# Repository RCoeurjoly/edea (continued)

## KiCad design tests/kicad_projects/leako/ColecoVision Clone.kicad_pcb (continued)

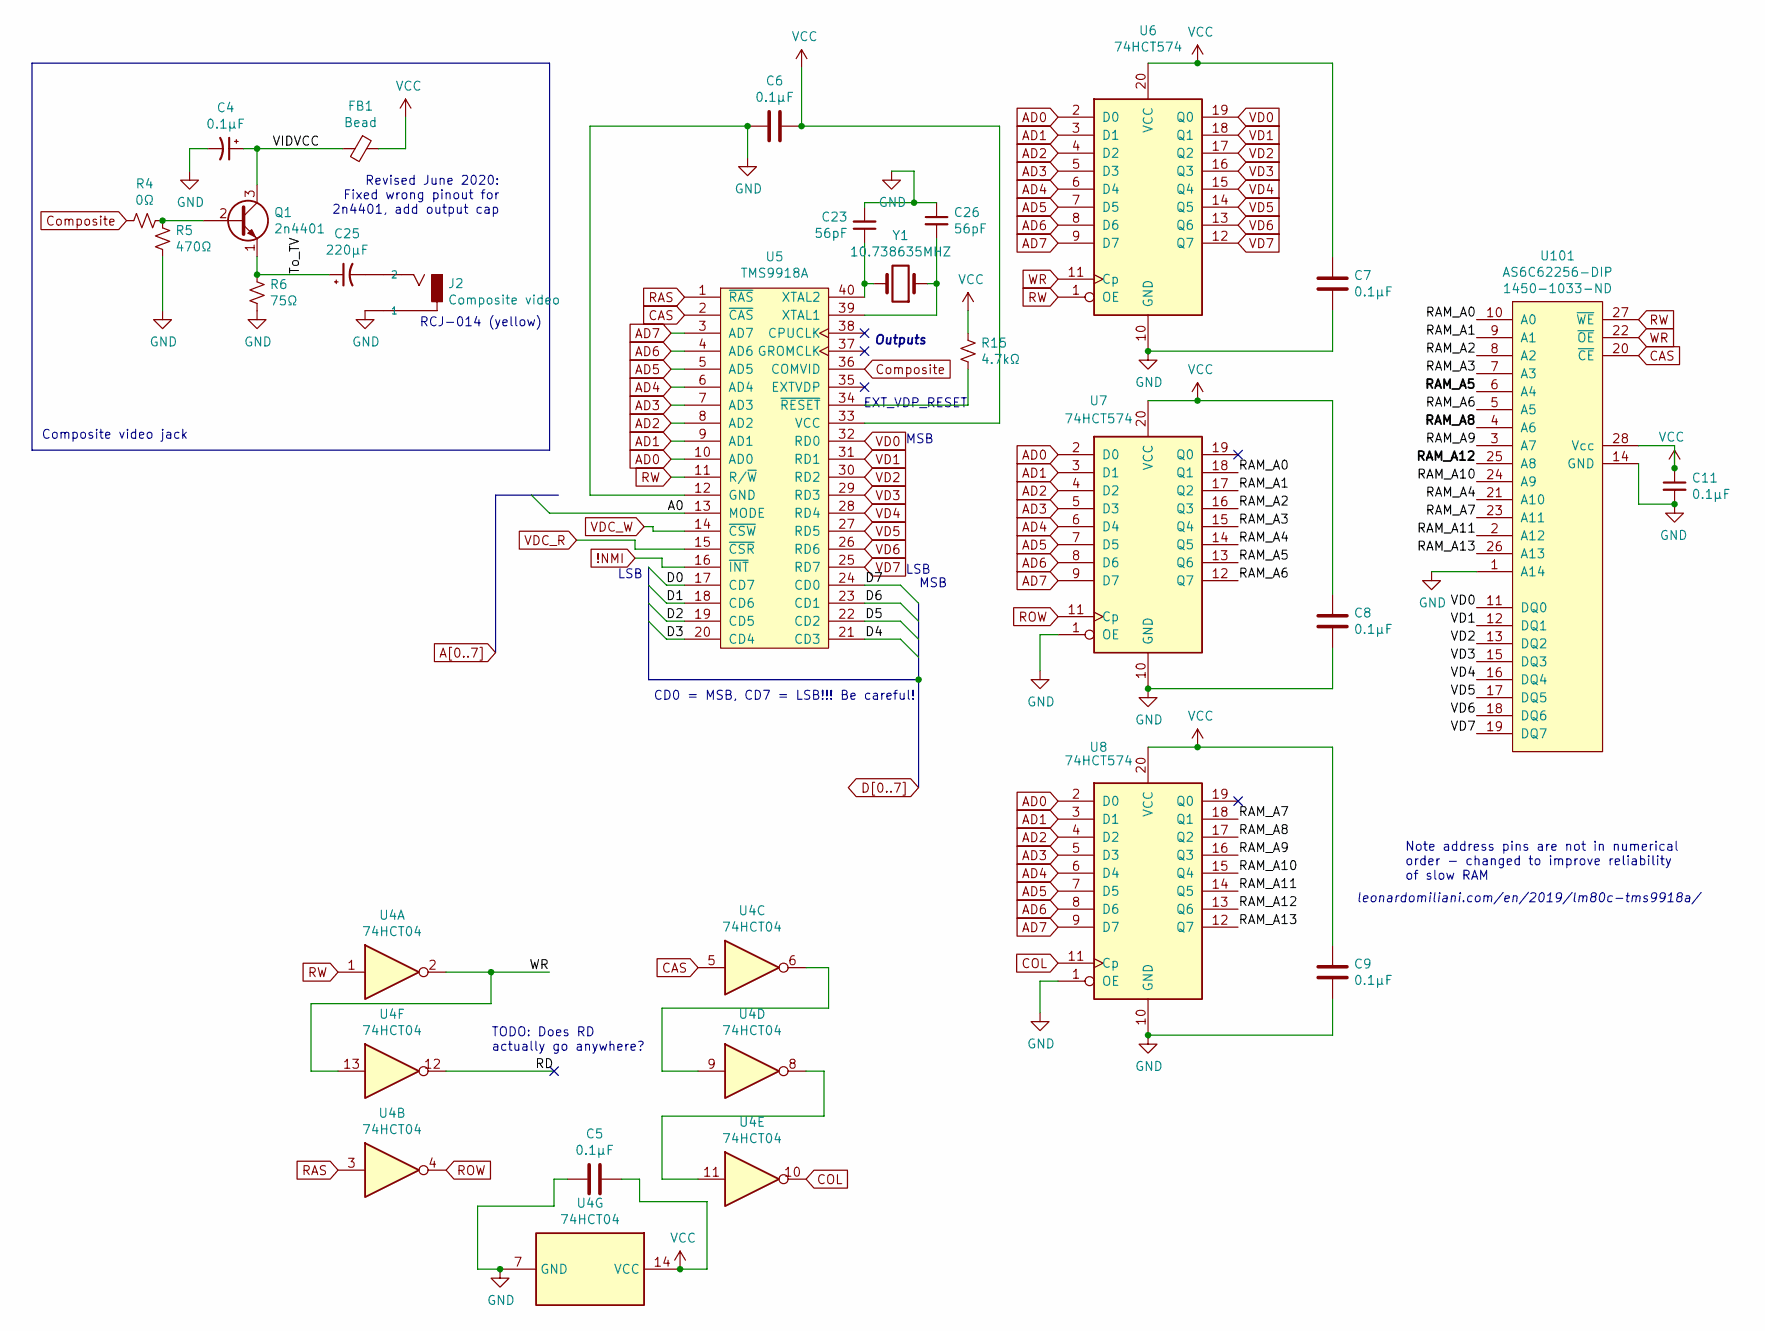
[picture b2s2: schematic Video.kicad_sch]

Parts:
C4, C5, C6, C7, C8, C9, C11: 0.1µF; C_0805_HandSoldering; DigiKey 1276-1099-1-ND
C23, C26: 56pF; C_0805_HandSoldering; DigiKey 732-7817-1-ND
C25: 220µF; CP_Radial_D6.3mm_P2.50mm; DigiKey 493-15121-ND
FB1: Bead; Choke_SMD_1206_Handsoldering; DigiKey 283-MFBW1V3216-310-RCT-ND
J2: Composite video; CUI_RCJ-017; DigiKey CP-1403-ND‎
Q1: 2n4401; TO-92_Inline_Wide; DigiKey 2N4401TFCT-ND
R4: 0Ω; R_0805_HandSoldering; DigiKey RMCF0805ZT0R00CT-ND
R5: 470Ω; R_0805_HandSoldering; DigiKey RMCF0805JT470RCT-ND
R6: 75Ω; R_0805_HandSoldering; DigiKey RMCF0805JT75R0CT-ND
R15: 4.7kΩ; R_0805_HandSoldering; DigiKey RMCF0805JT4K70CT-ND
U4: 74HCT04; SOIC-14_3.9x8.7mm_Pitch1.27mm; DigiKey 296-31832-1-ND
U5: TMS9918A; DIP-40_W15.24mm_Socket_LongPads; DigiKey ED3048-5-ND
U6, U7, U8: 74HCT574; SOIC-20W_7.5x12.8mm_P1.27mm_LongLegs; DigiKey 1727-2856-1-ND
U101: AS6C62256-DIP; DIP-28_W15.24mm_Socket_LongPads; DigiKey 1450-1033-ND
Y1: 10.738635MHZ; Crystal_HC49-U_Vertical; DigiKey CTX1443-ND

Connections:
!NMI: U5.16 (~INT); also elsewhere on the board
/Video/RAM_A0: U7.18 (Q1), U101.10 (A0)
/Video/RAM_A1: U7.17 (Q2), U101.9 (A1)
/Video/RAM_A2: U7.16 (Q3), U101.8 (A2)
/Video/RAM_A3: U7.15 (Q4), U101.7 (A3)
/Video/RAM_A4: U7.14 (Q5), U101.21 (A10)
/Video/RAM_A5: U7.13 (Q6), U101.6 (A4)
/Video/RAM_A6: U7.12 (Q7), U101.5 (A5)
/Video/RAM_A7: U8.18 (Q1), U101.23 (A11)
/Video/RAM_A8: U8.17 (Q2), U101.4 (A6)
/Video/RAM_A9: U8.16 (Q3), U101.3 (A7)
/Video/RAM_A10: U8.15 (Q4), U101.24 (A9)
/Video/RAM_A11: U8.14 (Q5), U101.2 (A12)
/Video/RAM_A12: U8.13 (Q6), U101.25 (A8)
/Video/RAM_A13: U8.12 (Q7), U101.26 (A13)
/Video/RD: U4.12
/Video/To_TV: C25.1, Q1.1 (E), R6.1
/Video/VIDVCC: C4.1, FB1.2, Q1.3 (C)
A0: U5.13 (MODE); also elsewhere on the board
AD0: U5.10 (AD0), U6.2 (D0), U7.2 (D0), U8.2 (D0)
AD1: U5.9 (AD1), U6.3 (D1), U7.3 (D1), U8.3 (D1)
AD2: U5.8 (AD2), U6.4 (D2), U7.4 (D2), U8.4 (D2)
AD3: U5.7 (AD3), U6.5 (D3), U7.5 (D3), U8.5 (D3)
AD4: U5.6 (AD4), U6.6 (D4), U7.6 (D4), U8.6 (D4)
AD5: U5.5 (AD5), U6.7 (D5), U7.7 (D5), U8.7 (D5)
AD6: U5.4 (AD6), U6.8 (D6), U7.8 (D6), U8.8 (D6)
AD7: U5.3 (AD7), U6.9 (D7), U7.9 (D7), U8.9 (D7)
CAS: U4.5, U5.2 (~CAS), U101.20 (~CE)
COL: U4.10, U8.11 (Cp)
Composite: R4.2, U5.36 (COMVID)
D0: U5.17 (CD7); also elsewhere on the board
D1: U5.18 (CD6); also elsewhere on the board
D2: U5.19 (CD5); also elsewhere on the board
D3: U5.20 (CD4); also elsewhere on the board
D4: U5.21 (CD3); also elsewhere on the board
D5: U5.22 (CD2); also elsewhere on the board
D6: U5.23 (CD1); also elsewhere on the board
D7: U5.24 (CD0); also elsewhere on the board
GND: C4.2, C5.2, C6.2, C7.2, C8.2, C9.2, C11.2, C23.2, C26.1, J2.1A (1), J2.1B (1), J2.1C (1), R5.2, R6.2, U4.7 (GND), U5.12 (GND), U6.10 (GND), U7.1 (OE), U7.10 (GND), U8.1 (OE), U8.10 (GND), U101.1 (A14), U101.14 (GND); also elsewhere on the board
unnamed: C23.1, U5.40 (XTAL2), Y1.2
unnamed: C25.2, J2.2
unnamed: C26.2, U5.39 (XTAL1), Y1.1
unnamed: Q1.2 (B), R4.1, R5.1
unnamed: R15.2, U5.34 (~RESET)
unnamed: U4.6, U4.9
unnamed: U4.8, U4.11
RAS: U4.3, U5.1 (~RAS)
ROW: U4.4, U7.11 (Cp)
RW: U4.1, U5.11 (R/~W), U6.1 (OE), U101.27 (~WE)
VCC: C5.1, C6.1, C7.1, C8.1, C9.1, C11.1, FB1.1, R15.1, U4.14 (VCC), U5.33 (VCC), U6.20 (VCC), U7.20 (VCC), U8.20 (VCC), U101.28 (Vcc); also elsewhere on the board
VD0: U5.32 (RD0), U6.19 (Q0), U101.11 (DQ0)
VD1: U5.31 (RD1), U6.18 (Q1), U101.12 (DQ1)
VD2: U5.30 (RD2), U6.17 (Q2), U101.13 (DQ2)
VD3: U5.29 (RD3), U6.16 (Q3), U101.15 (DQ3)
VD4: U5.28 (RD4), U6.15 (Q4), U101.16 (DQ4)
VD5: U5.27 (RD5), U6.14 (Q5), U101.17 (DQ5)
VD6: U5.26 (RD6), U6.13 (Q6), U101.18 (DQ6)
VD7: U5.25 (RD7), U6.12 (Q7), U101.19 (DQ7)
VDC_R: U5.15 (~CSR); also elsewhere on the board
VDC_W: U5.14 (~CSW); also elsewhere on the board
WR: U4.2, U4.13, U6.11 (Cp), U101.22 (~OE)

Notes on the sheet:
leonardomiliani.com/en/2019/lm80c-tms9918a/
TODO: Does RD actually go anywhere?
EXT_VDP_RESET
LSB
CD0 = MSB, CD7 = LSB!!! Be careful!
Composite video jack
Note address pins are not in numerical order - changed to improve reliability of slow RAM
RCJ-014 (yellow)
Revised June 2020: Fixed wrong pinout for 2n4401, add output cap
MSB
Outputs

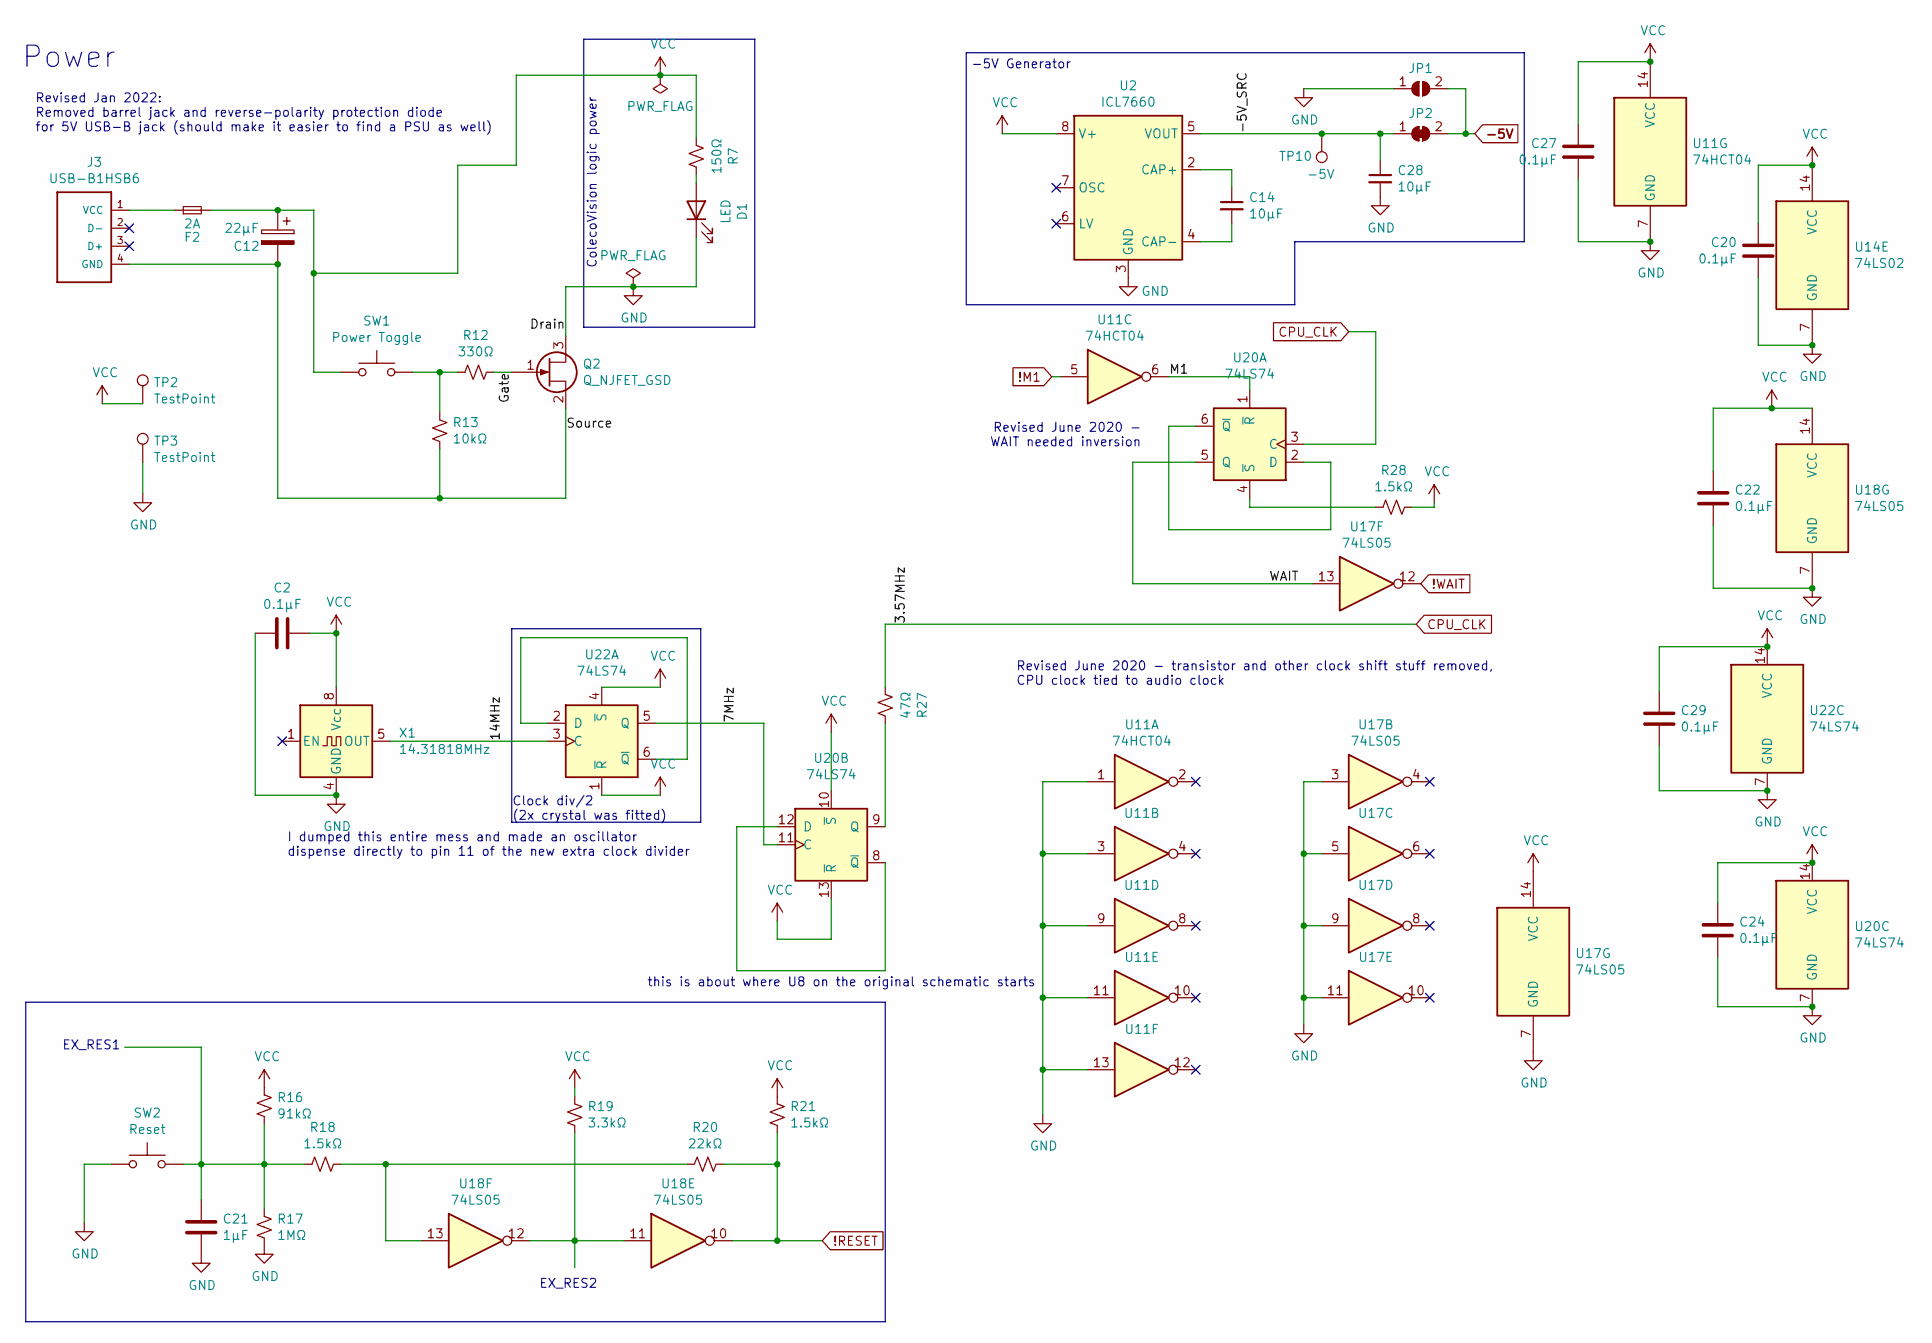
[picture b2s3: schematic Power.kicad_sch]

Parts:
C2, C20, C22, C24, C27, C29: 0.1µF; C_0805_HandSoldering; DigiKey 1276-1099-1-ND
C12: 22µF; CP_Radial_D5.0mm_P2.50mm; DigiKey 493-1037-ND
C14, C28: 10µF; C_0805_2012Metric_Pad1.15x1.40mm_HandSolder; DigiKey 1276-1298-1-ND
C21: 1µF; C_0805_HandSoldering; DigiKey 1276-2926-1-ND
D1: LED; LED_D3.0mm; DigiKey 1497-1022-ND
F2: 2A; 0251002.MRT1L; DigiKey F3171CT-ND
J3: USB-B1HSB6; OST_USB-B1HSB6; DigiKey ED2982-ND
JP1: SolderJumper_2_Open; SolderJumper-2_P1.3mm_Open_Pad1.0x1.5mm
JP2: SolderJumper_2_Bridged; SolderJumper-2_P1.3mm_Bridged_Pad1.0x1.5mm
Q2: Q_NJFET_GSD; SOT-23_Handsoldering; DigiKey DMN2046U-7DICT-ND
R7: 150Ω; R_0805_HandSoldering; DigiKey RMCF0805JT150RCT-ND
R12: 330Ω; R_0805_HandSoldering; DigiKey RMCF0805JT330RCT-ND
R13: 10kΩ; R_0805_HandSoldering; DigiKey RMCF0805JT10K0CT-ND
R16: 91kΩ; R_0805_HandSoldering; DigiKey RMCF0805JT91K0CT-ND
R17: 1MΩ; R_0805_HandSoldering; DigiKey RMCF0805JT1M00CT-ND
R18, R21, R28: 1.5kΩ; R_0805_HandSoldering; DigiKey RMCF0805FT1K00CT-ND
R19: 3.3kΩ; R_0805_HandSoldering; DigiKey RMCF0805JT3K30CT-ND
R20: 22kΩ; R_0805_HandSoldering; DigiKey RMCF0805JT22K0CT-ND
R27: 47Ω; R_0805_HandSoldering; DigiKey RMCF0805JT47R0CT-ND
SW1: Power Toggle; PVA1_Switch; DigiKey 401-1132-ND
SW2: Reset; SW_PUSH_6mm; DigiKey 679-2428-ND
TP2, TP3: TestPoint; Measurement_Point_Round-TH_Small
TP10: -5V; TestPoint_Loop_D1.80mm_Drill1.0mm_Beaded
U2: ICL7660; SOIC-8_3.9x4.9mm_P1.27mm; DigiKey ICL7660CSA+TCT-ND
U11: 74HCT04; SOIC-14_3.9x8.7mm_Pitch1.27mm; DigiKey 296-31832-1-ND
U14: 74LS02; SOIC-14_3.9x8.7mm_Pitch1.27mm; DigiKey 296-14874-1-ND
U17: 74LS05; DigiKey 296-1630-1-ND
U18: 74LS05; SOIC-14_3.9x8.7mm_Pitch1.27mm; DigiKey 296-1630-1-ND
U20, U22: 74LS74; SOIC-14_3.9x8.7mm_Pitch1.27mm; DigiKey 296-14899-1-ND
X1: 14.31818MHz; Oscillator_DIP-8_LargePads; DigiKey 535-9170-5-ND

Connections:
!M1: U11.5; also elsewhere on the board
!RESET: R20.1, R21.2, U18.10; also elsewhere on the board
!WAIT: U17.12; also elsewhere on the board
-5V: JP1.2 (B), JP2.2 (B); also elsewhere on the board
/Power/7MHz: U20.11 (C), U22.5 (Q)
/Power/14MHz: U22.3 (C), X1.5 (OUT)
/Power/-5V_SRC: C28.1, JP2.1 (A), TP10.1, U2.5 (VOUT)
/Power/Gate: Q2.1 (G), R12.1
/Power/M1: U11.6, U20.1 (~R)
/Power/Source: C12.2, J3.4 (GND), Q2.2 (S), R13.2
/Power/WAIT: U17.13, U20.5 (Q)
CPU_CLK: R27.2, U20.3 (C); also elsewhere on the board
GND: C2.2, C20.1, C21.2, C22.2, C24.2, C27.1, C28.2, C29.2, D1.1 (K), JP1.1 (A), Q2.3 (D), R17.2, SW2.1, TP3.1, U2.3 (GND), U11.1, U11.3, U11.7 (GND), U11.9, U11.11, U11.13, U14.7 (GND), U17.3, U17.5, U17.7 (GND), U17.9, U17.11, U18.7 (GND), U20.7 (GND), U22.7 (GND), X1.4 (GND); also elsewhere on the board
unnamed: C14.1, U2.2 (CAP+)
unnamed: C14.2, U2.4 (CAP-)
unnamed: C21.1, R16.2, R17.1, R18.2, SW2.2
unnamed: D1.2 (A), R7.1
unnamed: F2.1, J3.1 (VCC)
unnamed: R12.2, R13.1, SW1.2
unnamed: R18.1, R20.2, U18.13
unnamed: R19.2, U18.11, U18.12
unnamed: R27.1, U20.9 (Q)
unnamed: R28.2, U20.4 (~S)
unnamed: U20.2 (D), U20.6 (~Q)
unnamed: U20.8 (~Q), U20.12 (D)
unnamed: U22.2 (D), U22.6 (~Q)
VCC: C2.1, C12.1, C20.2, C22.1, C24.1, C27.2, C29.1, F2.2, R7.2, R16.1, R19.1, R21.1, R28.1, SW1.1, TP2.1, U2.8 (V+), U11.14 (VCC), U14.14 (VCC), U17.14 (VCC), U18.14 (VCC), U20.10 (~S), U20.13 (~R), U20.14 (VCC), U22.1 (~R), U22.4 (~S), U22.14 (VCC), X1.8 (Vcc); also elsewhere on the board

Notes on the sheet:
Power
Revised June 2020 - WAIT needed inversion
ColecoVision logic power
I dumped this entire mess and made an oscillator dispense directly to pin 11 of the new extra clock divider
EX_RES2
Revised June 2020 - transistor and other clock shift stuff removed, CPU clock tied to audio clock
Clock div/2 (2x crystal was fitted)
Revised Jan 2022: Removed barrel jack and reverse-polarity protection diode for 5V USB-B jack (should make it easier to find a PSU as well)
EX_RES1
this is about where U8 on the original schematic starts
-5V Generator

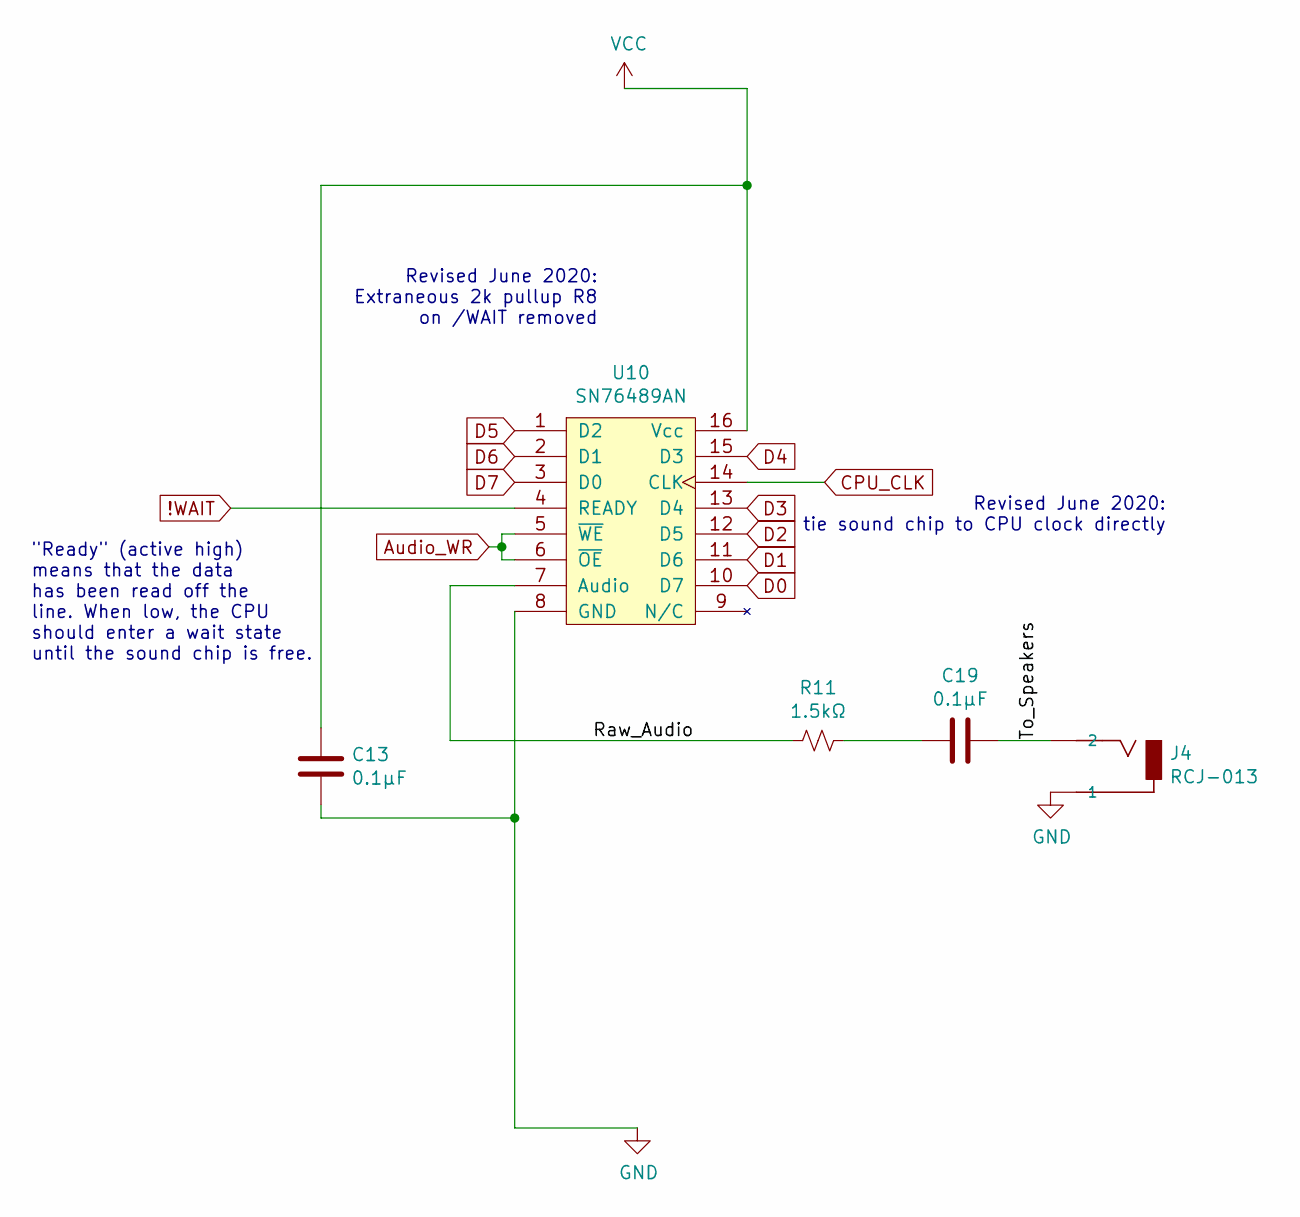
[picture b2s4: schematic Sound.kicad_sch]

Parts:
C13, C19: 0.1µF; C_0805_HandSoldering; DigiKey 1276-1099-1-ND
J4: RCJ-013; CUI_RCJ-017; DigiKey CP-1402-ND‎
R11: 1.5kΩ; R_0805_HandSoldering; DigiKey RMCF0805FT1K00CT-ND
U10: SN76489AN; DIP-16_W7.62mm_Socket_LongPads; DigiKey AE9992-ND

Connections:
!WAIT: U10.4 (READY); also elsewhere on the board
/Sound/Raw_Audio: R11.2, U10.7 (Audio)
/Sound/To_Speakers: C19.1, J4.2
Audio_WR: U10.5 (~WE), U10.6 (~OE); also elsewhere on the board
CPU_CLK: U10.14 (CLK); also elsewhere on the board
D0: U10.10 (D7); also elsewhere on the board
D1: U10.11 (D6); also elsewhere on the board
D2: U10.12 (D5); also elsewhere on the board
D3: U10.13 (D4); also elsewhere on the board
D4: U10.15 (D3); also elsewhere on the board
D5: U10.1 (D2); also elsewhere on the board
D6: U10.2 (D1); also elsewhere on the board
D7: U10.3 (D0); also elsewhere on the board
GND: C13.2, J4.1A (1), J4.1B (1), J4.1C (1), U10.8 (GND); also elsewhere on the board
unnamed: C19.2, R11.1
VCC: C13.1, U10.16 (Vcc); also elsewhere on the board

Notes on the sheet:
"Ready" (active high) means that the data has been read off the line. When low, the CPU should enter a wait state until the sound chip is free.
Revised June 2020: Extraneous 2k pullup R8 on /WAIT removed
Revised June 2020: tie sound chip to CPU clock directly

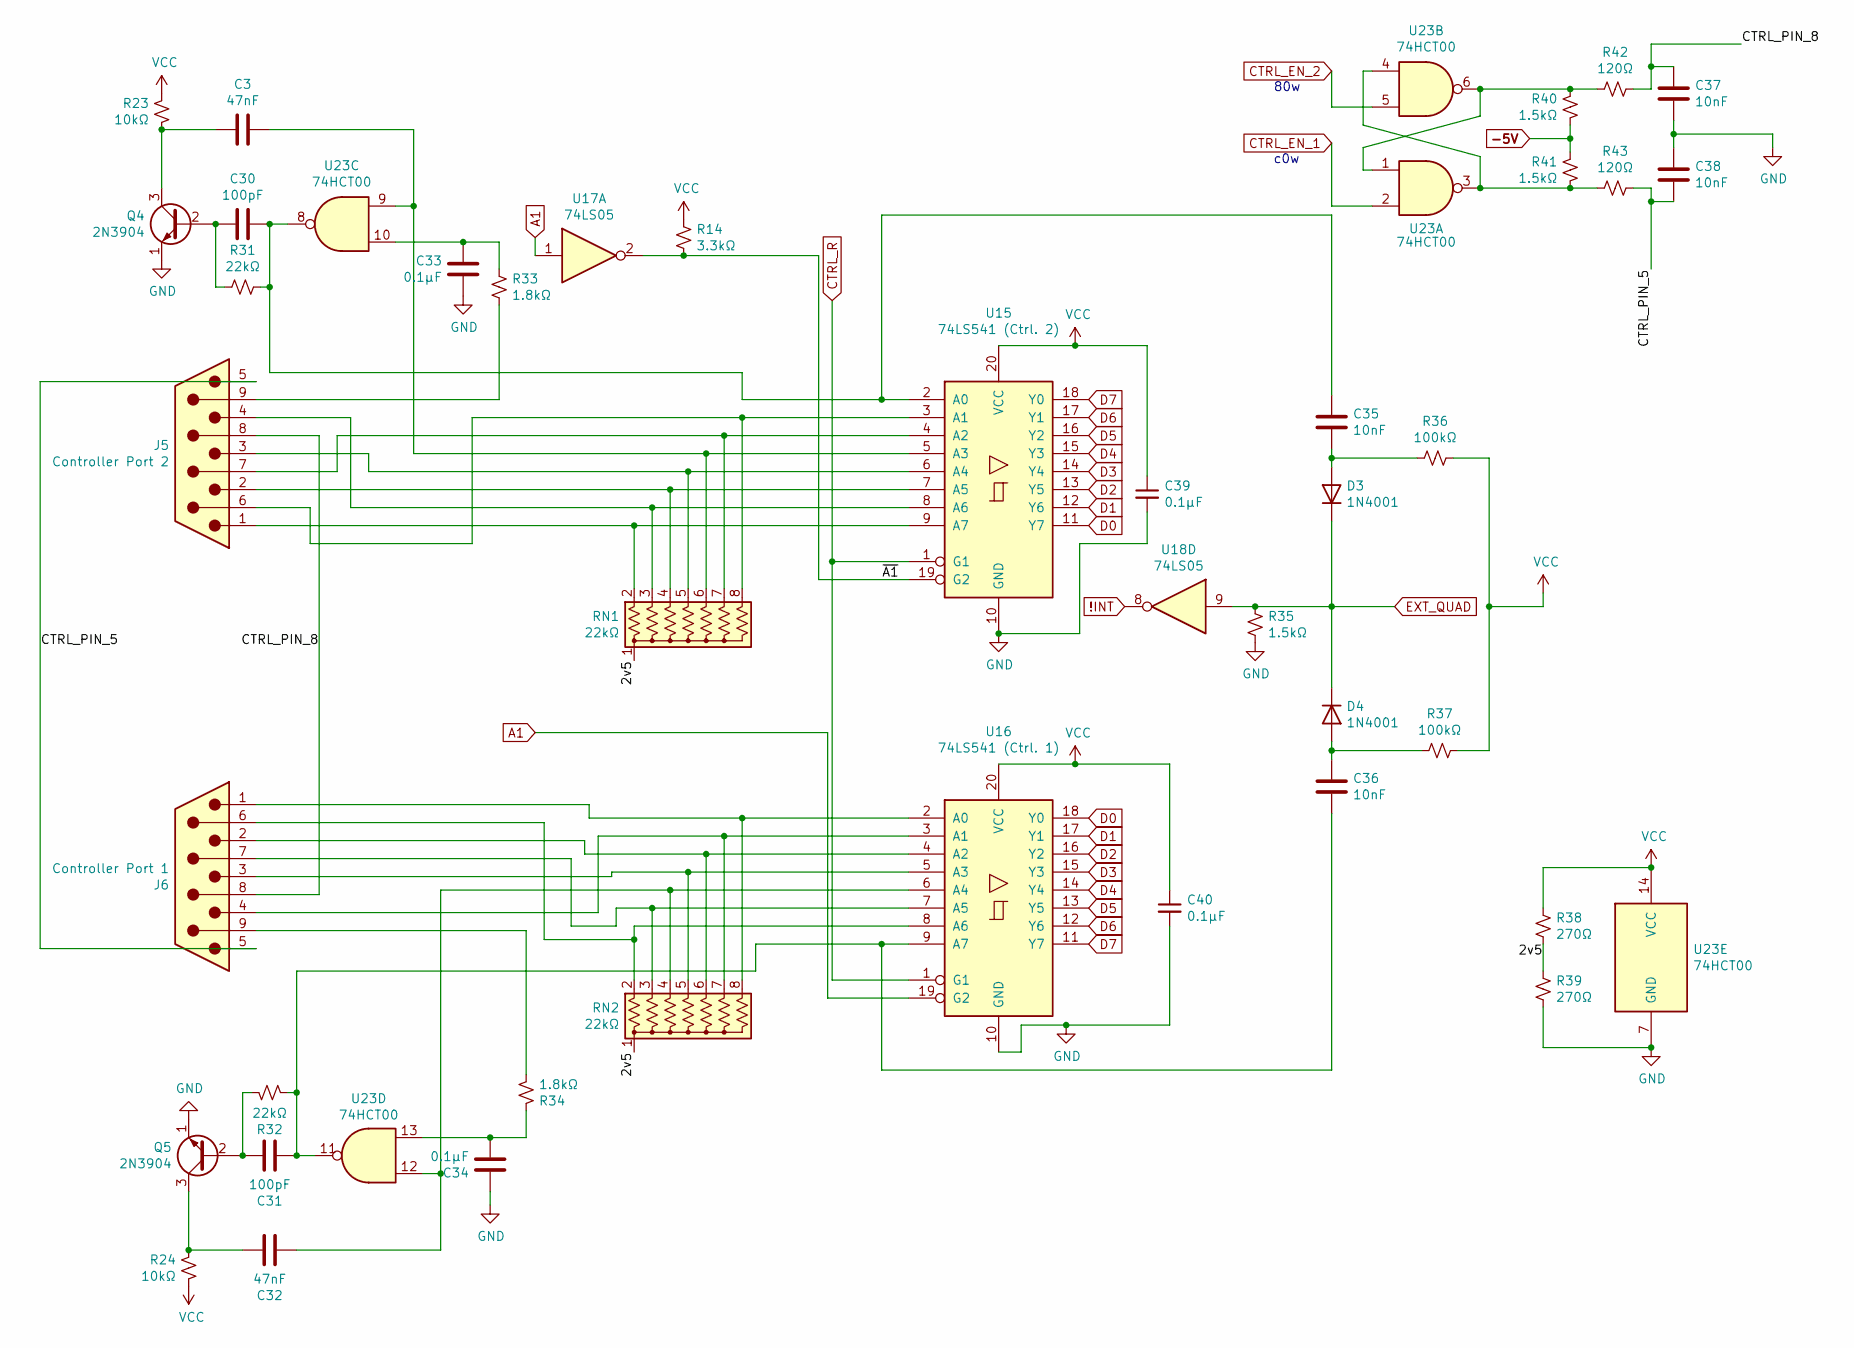
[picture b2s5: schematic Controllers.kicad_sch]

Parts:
C3, C32: 47nF; C_0805_HandSoldering; DigiKey 732-8059-1-ND
C30, C31: 100pF; C_0805_HandSoldering; DigiKey 732-12161-1-ND
C33, C34: 0.1µF; C_0805_HandSoldering; DigiKey 1276-1099-1-ND
C35, C36, C37, C38: 10nF; C_0805_HandSoldering; DigiKey 399-C0805X103K1RAC3316CT-ND
C39, C40: 0.1µF; C_0805_2012Metric_Pad1.15x1.40mm_HandSolder; DigiKey 1276-1099-1-ND
D3, D4: 1N4001; D_DO-41_SOD81_P2.54mm_Vertical_AnodeUp; DigiKey 641-1310-1-ND
J5: Controller Port 2; A-DS 09 A-KG-T2S; DigiKey AE10968-ND
J6: Controller Port 1; A-DS 09 A-KG-T2S; DigiKey AE10968-ND
Q4, Q5: 2N3904; TO-92_Inline_Wide; DigiKey 2N3904TAFSCT-ND
R14: 3.3kΩ; R_0805_HandSoldering; DigiKey RMCF0805JT3K30CT-ND
R23, R24: 10kΩ; R_0805_HandSoldering; DigiKey RMCF0805JT10K0CT-ND
R31, R32: 22kΩ; R_0805_HandSoldering; DigiKey RMCF0805JT22K0CT-ND
R33, R34: 1.8kΩ; R_0805_HandSoldering; DigiKey RMCF0805JT1K80CT-ND
R35, R40, R41: 1.5kΩ; R_0805_HandSoldering; DigiKey RMCF0805JT1K50CT-ND
R36, R37: 100kΩ; R_0805_HandSoldering; DigiKey RMCF0805JT100KCT-ND
R38, R39: 270Ω; R_0805_HandSoldering; DigiKey RMCF0805JT270RCT-ND
R42, R43: 120Ω; R_0805_HandSoldering; DigiKey RMCF0805JT120RCT-ND
RN1, RN2: 22kΩ; R_Array_SIP8; DigiKey 4608X-1-223LF-ND
U15: 74LS541 (Ctrl. 2); SOIC-20W_7.5x12.8mm_P1.27mm; DigiKey 296-14870-1-ND
U16: 74LS541 (Ctrl. 1); SOIC-20W_7.5x12.8mm_P1.27mm; DigiKey 296-14870-1-ND
U17, U18: 74LS05; SOIC-14_3.9x8.7mm_Pitch1.27mm; DigiKey 296-1630-1-ND
U23: 74HCT00; SOIC-14_3.9x8.7mm_Pitch1.27mm; DigiKey 296-14542-1-ND

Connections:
!INT: U18.8; also elsewhere on the board
-5V: R40.1, R41.2; also elsewhere on the board
/Controllers/2v5: R38.2, R39.1, RN1.1 (common), RN2.1 (common)
/Controllers/CTRL_PIN_5: C38.2, J5.5, J6.5, R43.1
/Controllers/CTRL_PIN_8: C37.1, J5.8, J6.8, R42.1
/Controllers/~A1: R14.2, U15.19 (G2), U17.2
A1: U16.19 (G2), U17.1; also elsewhere on the board
CTRL_EN_1: U23.2; also elsewhere on the board
CTRL_EN_2: U23.5; also elsewhere on the board
CTRL_R: U15.1 (G1), U16.1 (G1); also elsewhere on the board
D0: U15.11 (Y7), U16.18 (Y0); also elsewhere on the board
D1: U15.12 (Y6), U16.17 (Y1); also elsewhere on the board
D2: U15.13 (Y5), U16.16 (Y2); also elsewhere on the board
D3: U15.14 (Y4), U16.15 (Y3); also elsewhere on the board
D4: U15.15 (Y3), U16.14 (Y4); also elsewhere on the board
D5: U15.16 (Y2), U16.13 (Y5); also elsewhere on the board
D6: U15.17 (Y1), U16.12 (Y6); also elsewhere on the board
D7: U15.18 (Y0), U16.11 (Y7); also elsewhere on the board
EXT_QUAD: D3.1 (K), D4.1 (K), R35.2, U18.9; also elsewhere on the board
GND: C33.1, C34.2, C37.2, C38.1, C39.2, C40.2, Q4.1 (E), Q5.1 (E), R35.1, R39.2, U15.10 (GND), U16.10 (GND), U23.7 (GND); also elsewhere on the board
unnamed: C3.1, RN1.6 (R5), U15.5 (A3), U23.9
unnamed: C3.2, Q4.3 (C), R23.1
unnamed: C30.1, C35.1, R31.1, U15.2 (A0), U23.8
unnamed: C30.2, Q4.2 (B), R31.2
unnamed: C31.1, C36.2, R32.1, U16.9 (A7), U23.11
unnamed: C31.2, Q5.2 (B), R32.2
unnamed: C32.1, RN2.4 (R3), U16.6 (A4), U23.12
unnamed: C32.2, Q5.3 (C), R24.2
unnamed: C33.2, R33.2, U23.10
unnamed: C34.1, R34.2, U23.13
unnamed: C35.2, D3.2 (A), R36.2
unnamed: C36.1, D4.2 (A), R37.2
unnamed: J5.1, RN1.2 (R1), U15.9 (A7)
unnamed: J5.2, RN1.4 (R3), U15.7 (A5)
unnamed: J5.3, RN1.5 (R4), U15.6 (A4)
unnamed: J5.4, RN1.3 (R2), U15.8 (A6)
unnamed: J5.6, RN1.8 (R7), U15.3 (A1)
unnamed: J5.7, RN1.7 (R6), U15.4 (A2)
unnamed: J5.9, R33.1
unnamed: J6.1, RN2.8 (R7), U16.2 (A0)
unnamed: J6.2, RN2.6 (R5), U16.4 (A2)
unnamed: J6.3, RN2.5 (R4), U16.5 (A3)
unnamed: J6.4, RN2.7 (R6), U16.3 (A1)
unnamed: J6.6, RN2.2 (R1), U16.8 (A6)
unnamed: J6.7, RN2.3 (R2), U16.7 (A5)
unnamed: J6.9, R34.1
unnamed: R40.2, R42.2, U23.1, U23.6
unnamed: R41.1, R43.2, U23.3, U23.4
VCC: C39.1, C40.1, R14.1, R23.2, R24.1, R36.1, R37.1, R38.1, U15.20 (VCC), U16.20 (VCC), U23.14 (VCC); also elsewhere on the board

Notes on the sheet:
c0w
80w

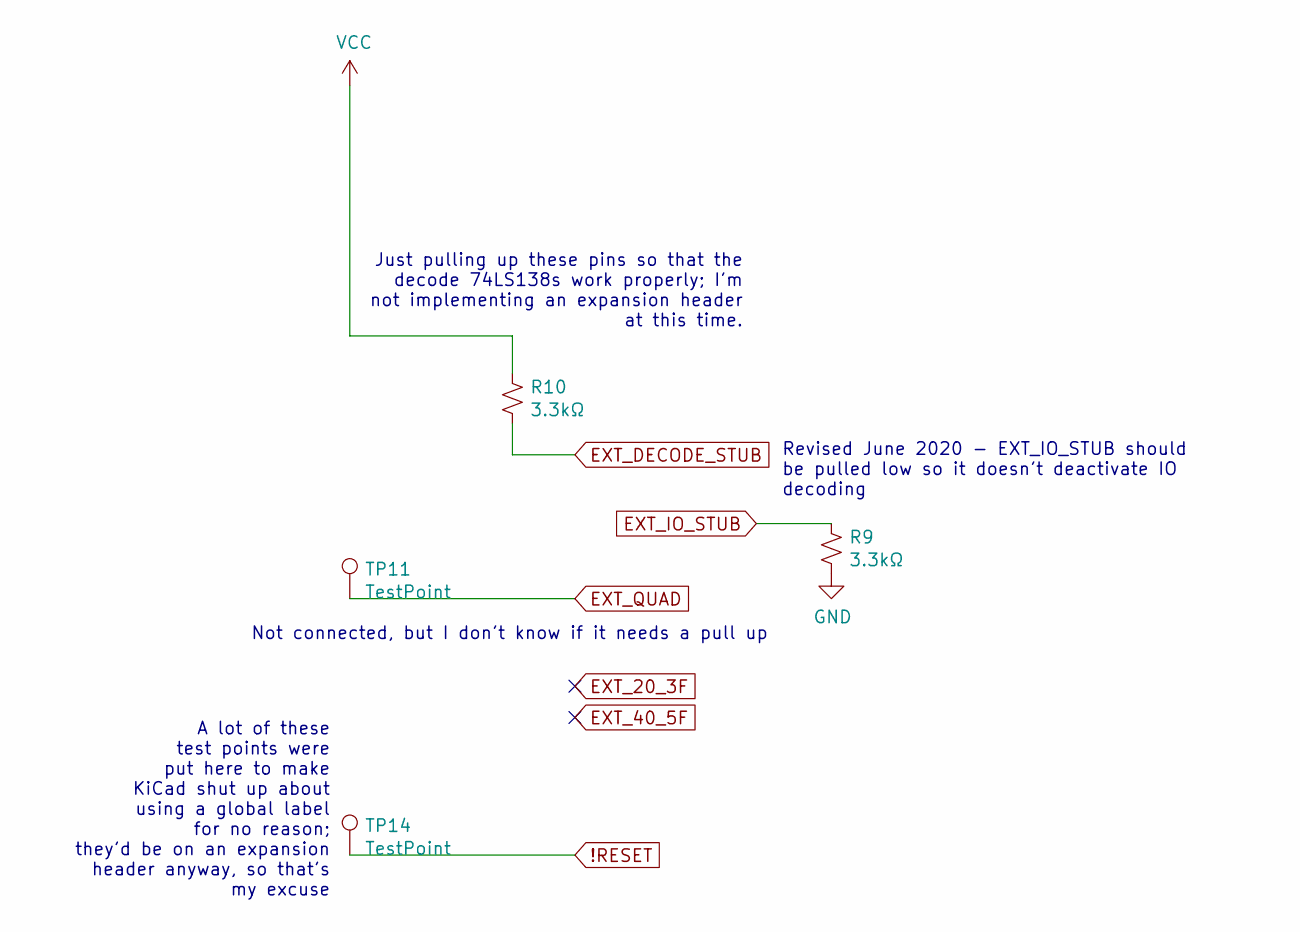
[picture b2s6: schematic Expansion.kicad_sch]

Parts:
R9, R10: 3.3kΩ; R_0805_HandSoldering; DigiKey RMCF0805JT3K30CT-ND
TP11: TestPoint; Measurement_Point_Round-TH_Small
TP14: TestPoint; Measurement_Point_Round-SMD-Pad_Small

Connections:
!RESET: TP14.1; also elsewhere on the board
EXT_DECODE_STUB: R10.2; also elsewhere on the board
EXT_IO_STUB: R9.2; also elsewhere on the board
EXT_QUAD: TP11.1; also elsewhere on the board
GND: R9.1; also elsewhere on the board
VCC: R10.1; also elsewhere on the board

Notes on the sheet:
Just pulling up these pins so that the decode 74LS138s work properly; I'm not implementing an expansion header at this time.
A lot of these test points were put here to make KiCad shut up about using a global label for no reason; they'd be on an expansion header anyway, so that's my excuse
Revised June 2020 - EXT_IO_STUB should be pulled low so it doesn't deactivate IO decoding
Not connected, but I don't know if it needs a pull up

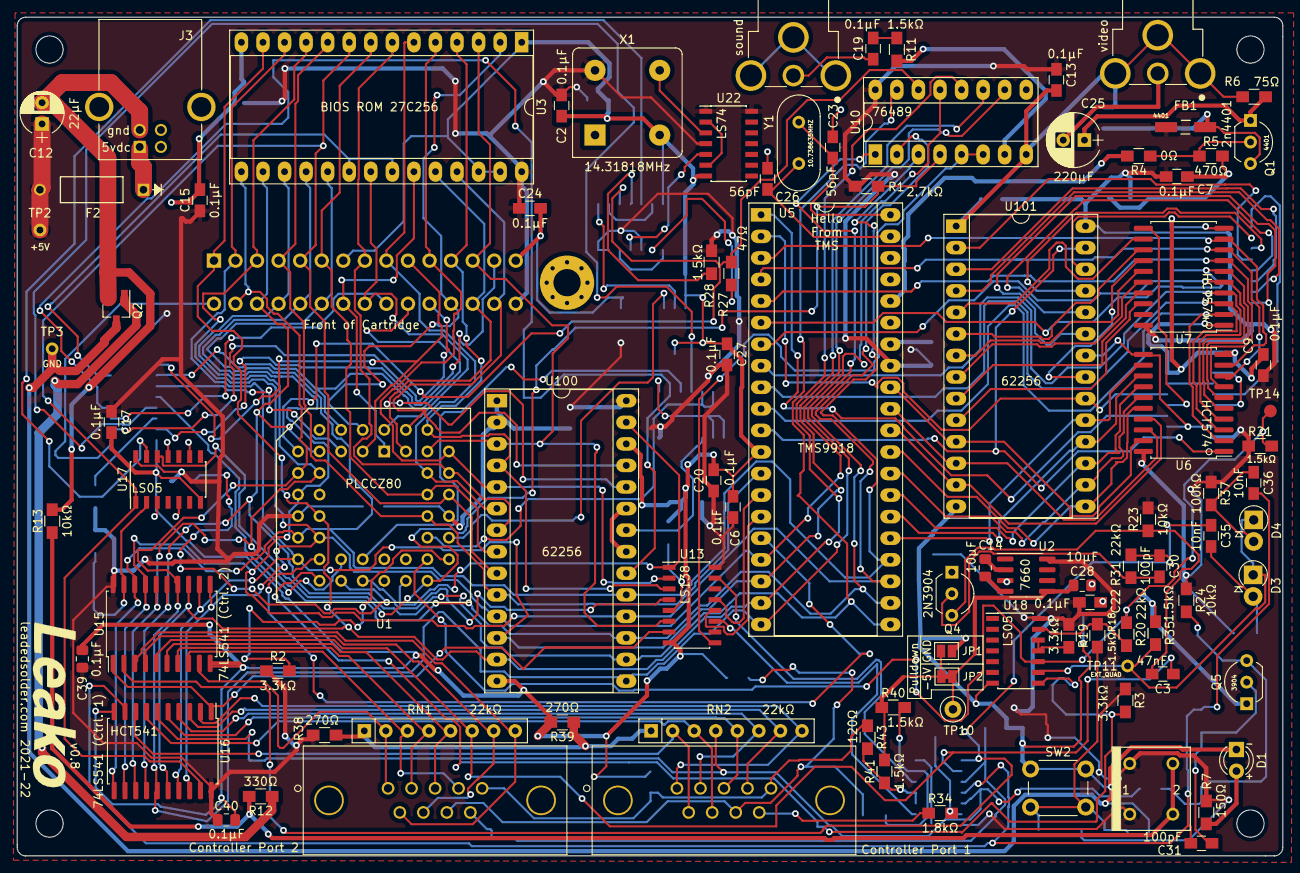
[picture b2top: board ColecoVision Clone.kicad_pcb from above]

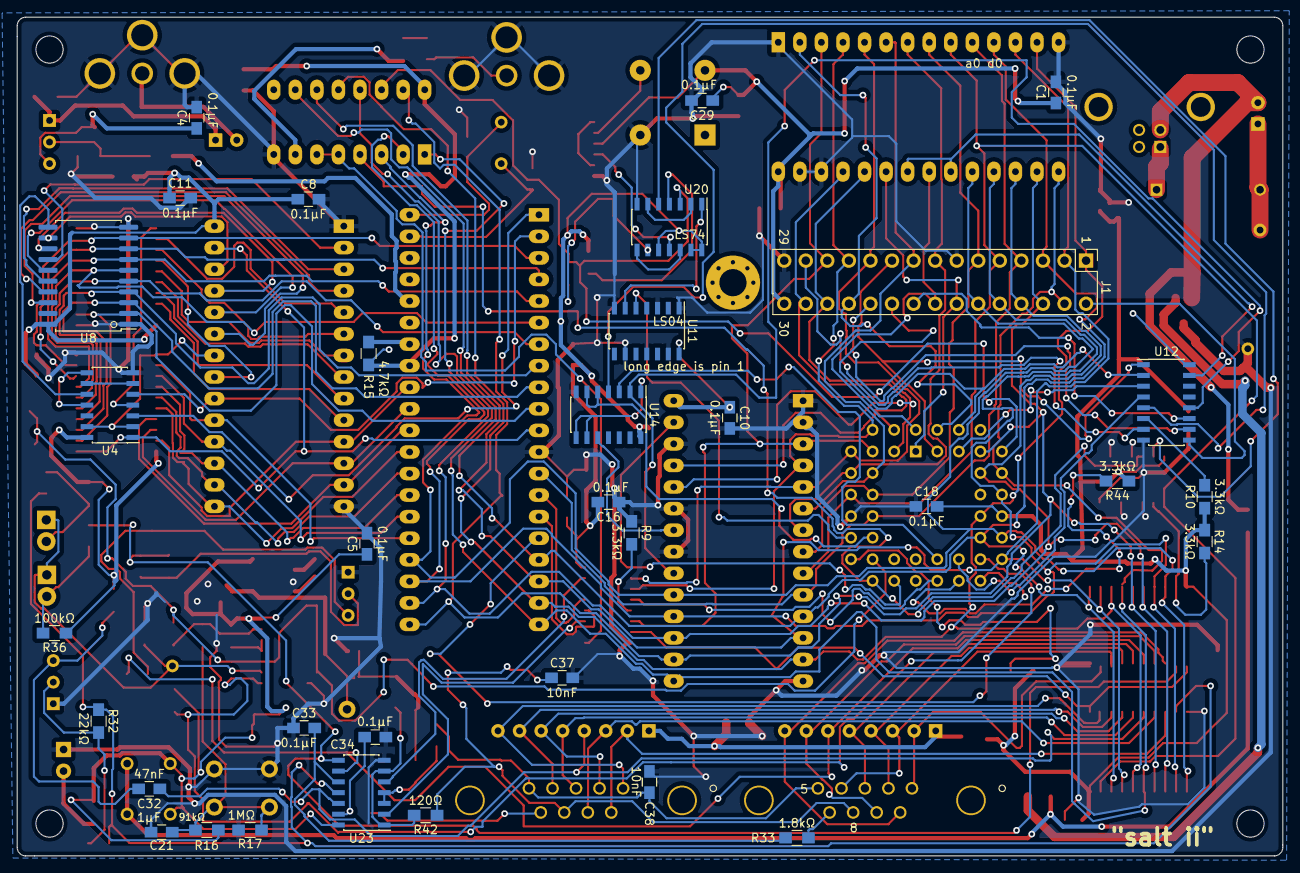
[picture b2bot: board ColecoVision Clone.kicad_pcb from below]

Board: 2 copper layers, 149.1 x 98.8 mm, 128 parts (34 on the bottom side), 159 nets.

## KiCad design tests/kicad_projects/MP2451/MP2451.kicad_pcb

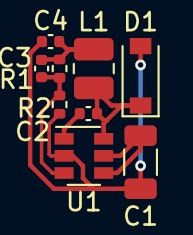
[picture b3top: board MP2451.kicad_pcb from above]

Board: 2 copper layers, 9 parts (0 on the bottom side), 6 nets.

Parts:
C1: 10uF; C_1206_3216Metric
C2: 100nF; C_0402_1005Metric
C3: 33pF; C_0402_1005Metric
C4: 10uF; C_0402_1005Metric
D1: 40V; D_SOD-123
L1: 2.2uH; L_1008_2520Metric
R1: 75k; R_0402_1005Metric
R2: 24k; R_0402_1005Metric
U1: MP2451; SOT-23-6

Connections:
+3V3: C3.2, C4.2, L1.2, R1.1
/FB: C3.1, R1.2, R2.1, U1.3
GND: C1.1, C4.1, D1.2, R2.2, U1.2
unnamed: C2.1, D1.1, L1.1, U1.6
unnamed: C2.2, U1.1
VBUS: C1.2, U1.4, U1.5

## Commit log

2022-09-27 Draw schematics as SVG using new Pydantic types
2022-09-28 Draw PCBs
2022-09-28 move drawable code back to parser due to circular import
    this will be fixed when we rewrite the PCB drawing code
    to use the Schematic drawing method
2022-09-29 add tool command to output SVGs
2022-09-30 Implement drawing of schematic "no connect"
2022-12-08 format code, fix some linter errors
2022-12-08 install pytest-xdist as a dev dependency
2023-03-28 Format files with black
2023-04-09 Cleanup: delete NOTES.md
2023-04-12 Update kicad6-test-files
2023-04-12 Fix sub symbol bezier
2023-04-12 Add hypothesis testing
2023-04-16 PCB parser
2023-04-16 Cache .hypothesis directory
2023-04-17 Refactor parsing
2023-04-17 Suppress hypothesis healthcheck
2023-04-18 Fix venv caching for Gitlab CI
2023-04-18 Move pcb layers definitions to `edea.types`
2023-04-19 Use monkey patch to keep hypothesis sizes down
2023-04-19 Add more linting
2023-04-19 Make image expression slightly more correct
2023-04-19 Remove redundant validator
2023-04-19 Remove another redundant validator
2023-04-21 Add long-running test script to gitlab ci
2023-04-21 Reduce long running tests to "types" module
2023-04-21 Fix names of tests for test-long-running in ci
2023-04-27 Restrict pylint to new code, make it happy
2023-04-28 Make tokens in tokenizer immutable by using tuple
2023-04-28 Use a recursive SExprList type
2023-04-28 Add types to tokenization
2023-05-03 Stop using pydantic.color.Color
2023-05-04 Render PCBs
2023-05-04 Implement serializer for types.common
2023-05-04 Replace pytest monkeypatch with `register_type_strategy`
2023-05-04 Remove useless asserts in test_create
2023-05-05 Replace `Is*` classes by using metadata
2023-05-05 Move `Stroke` to common
2023-05-06 Serialize union types
2023-05-09 Make pylint fail on any warnings/errors
2023-05-09 Add relative import checker to pylint
2023-05-09 Fix some bad validators
2023-05-15 Implement serializer for `schematic.symbol`
2023-05-15 Handle negative zero in `number_to_str`
2023-05-15 Implement serializer for schematics
2023-05-23 Auto generate EDeA docs and host it on gitlab pages
2023-06-19 Refactor KicadExpr __eq__
2023-06-19 Make serialization work for `pcb.common`
2023-06-19 Move equality stuff into private module
2023-06-19 Fix equality comparison of different length lists
2023-06-19 Replace asserts with isinstance for "at" from_list
2023-06-19 Add doctest for get_full_seq_type
2023-06-19 Update hypothesis
2023-06-24 Refactor handling of pcb layers
2023-06-25 Implement serializer for `pcb.graphics`
2023-06-25 Implement serializer for `types.pcb`
2023-07-06 Add nox
    install pytest-cov in the tox session
    not just tests
    site-packages
    poetry install
    poetry install only
2023-07-08 Make type unpacking compatible with py3.10
2023-07-11 Release a package to gitlab registry
2023-08-09 Add leako to tests
    Used for testing project metadata
2023-08-28 Add `Project` type
2023-09-13 Update kicad-test-files@dfb4bba197167ec308d85dbc24eab7f0f7008027
2023-09-13 Upload coverage reports
2023-09-13 Fix layer docs
2023-09-13 Fix docs deployment
2023-09-13 Calculate board outline size from graphical elements in `Edge.Cuts` layer
2023-11-02 Adjust `.gitlab-ci.yml` for the new version of CI runner
2023-11-12 Remove edea.draw
    Now a seperate module: https://gitlab.com/edea-dev/edea_draw
2023-11-12 Rename edea.types to edea.kicad
2023-11-12 Remove unused numpy import
2023-11-12 Revert "Remove unused numpy import"
    This reverts commit 56e587ececcb63ff14a87b6da49230c77a78a69b.
2023-11-12 Re-add numpy dependency
2023-11-12 Lock down pyright version
2023-11-18 Update `kicad.schematics` to KiCad 7
2023-11-25 Support python3.12
2023-12-07 Update `kicad.pcb` to kicad 7
2023-12-07 Re-implement parsing to be driven by the dataclass fields
2023-12-07 Make kicad_expr_tag_name a ClassVar
2023-12-07 Switch from dataclass metadata to typing.Annotated
2023-12-07 Fix hypothesis ambiguity around schematic project expressions
2023-12-07 Add a pydantic model for .kicad_pro
2023-12-07 Move kicad/project.py to metadata.py
2023-12-07 Tidy up
2023-12-07 Pluralize all the lists
2023-12-16 Add a `SchematicGroup` class to handle inserting sub schematics
2023-12-16 Add `insert_layout` method to `Pcb`
2024-01-12 Add cli that can do `edea add [folder-with-kicad-files]`
2024-02-19 Remote RC integration
2024-02-24 Switch to kicad-cli@8.0.0 for DRC and ERC
2024-02-26 Fix loading reports from JSON
2024-05-21 Introduce the cli subcommand `edea add`
2024-07-16 Add flake
2024-07-16 Try to use python3.11, does not work yet
2024-07-16 Use nixos-24.05 for nixpkgs, with good kicad
2024-07-17 Add setuptools to pyright
2024-07-17 Use ruff 0.5.1
2024-07-17 Fix some dependencies
2024-07-17 Use older setuptools, now nix build is succesful
2024-07-17 Add requests
2024-07-17 include kicad as build dep
2024-07-17 update versions
2024-07-22 updated lock file
2024-07-22 update ci
2024-07-29 Override before_script
2024-07-29 testing new ci
2024-07-29 nested images
2024-07-29 updated ci to remove stage and cache
2024-07-29 ### Fixed
    - Missing runtime dependencies in the `pyproject.toml` file.
    ### Added
    - Full dcoumentation.
2024-07-29 added cachix, if it works rerun the test
2024-07-29 fixed it using nix2 commands
2024-07-30 updated flake.nix to add extra-substuters just to test if cachix works
2024-07-30 Use cachix docker image
2024-07-30 Clean up switch to cachix image
2024-07-30 Update .gitlab-ci.yml file
2024-07-31 Draft: KiCad 8 support
2024-07-31 poetry lock
2024-07-31 Add nix the devcontainer
2024-08-01 updated ci to use main image
2024-08-01 breaking ci on purpose
2024-08-01 fixed ci on purpose
2024-08-01 reverted back to cachix image
2024-08-05 updated pyproject duplicate deps
2024-08-05 updated ruff again
2024-08-05 flake: update flake
